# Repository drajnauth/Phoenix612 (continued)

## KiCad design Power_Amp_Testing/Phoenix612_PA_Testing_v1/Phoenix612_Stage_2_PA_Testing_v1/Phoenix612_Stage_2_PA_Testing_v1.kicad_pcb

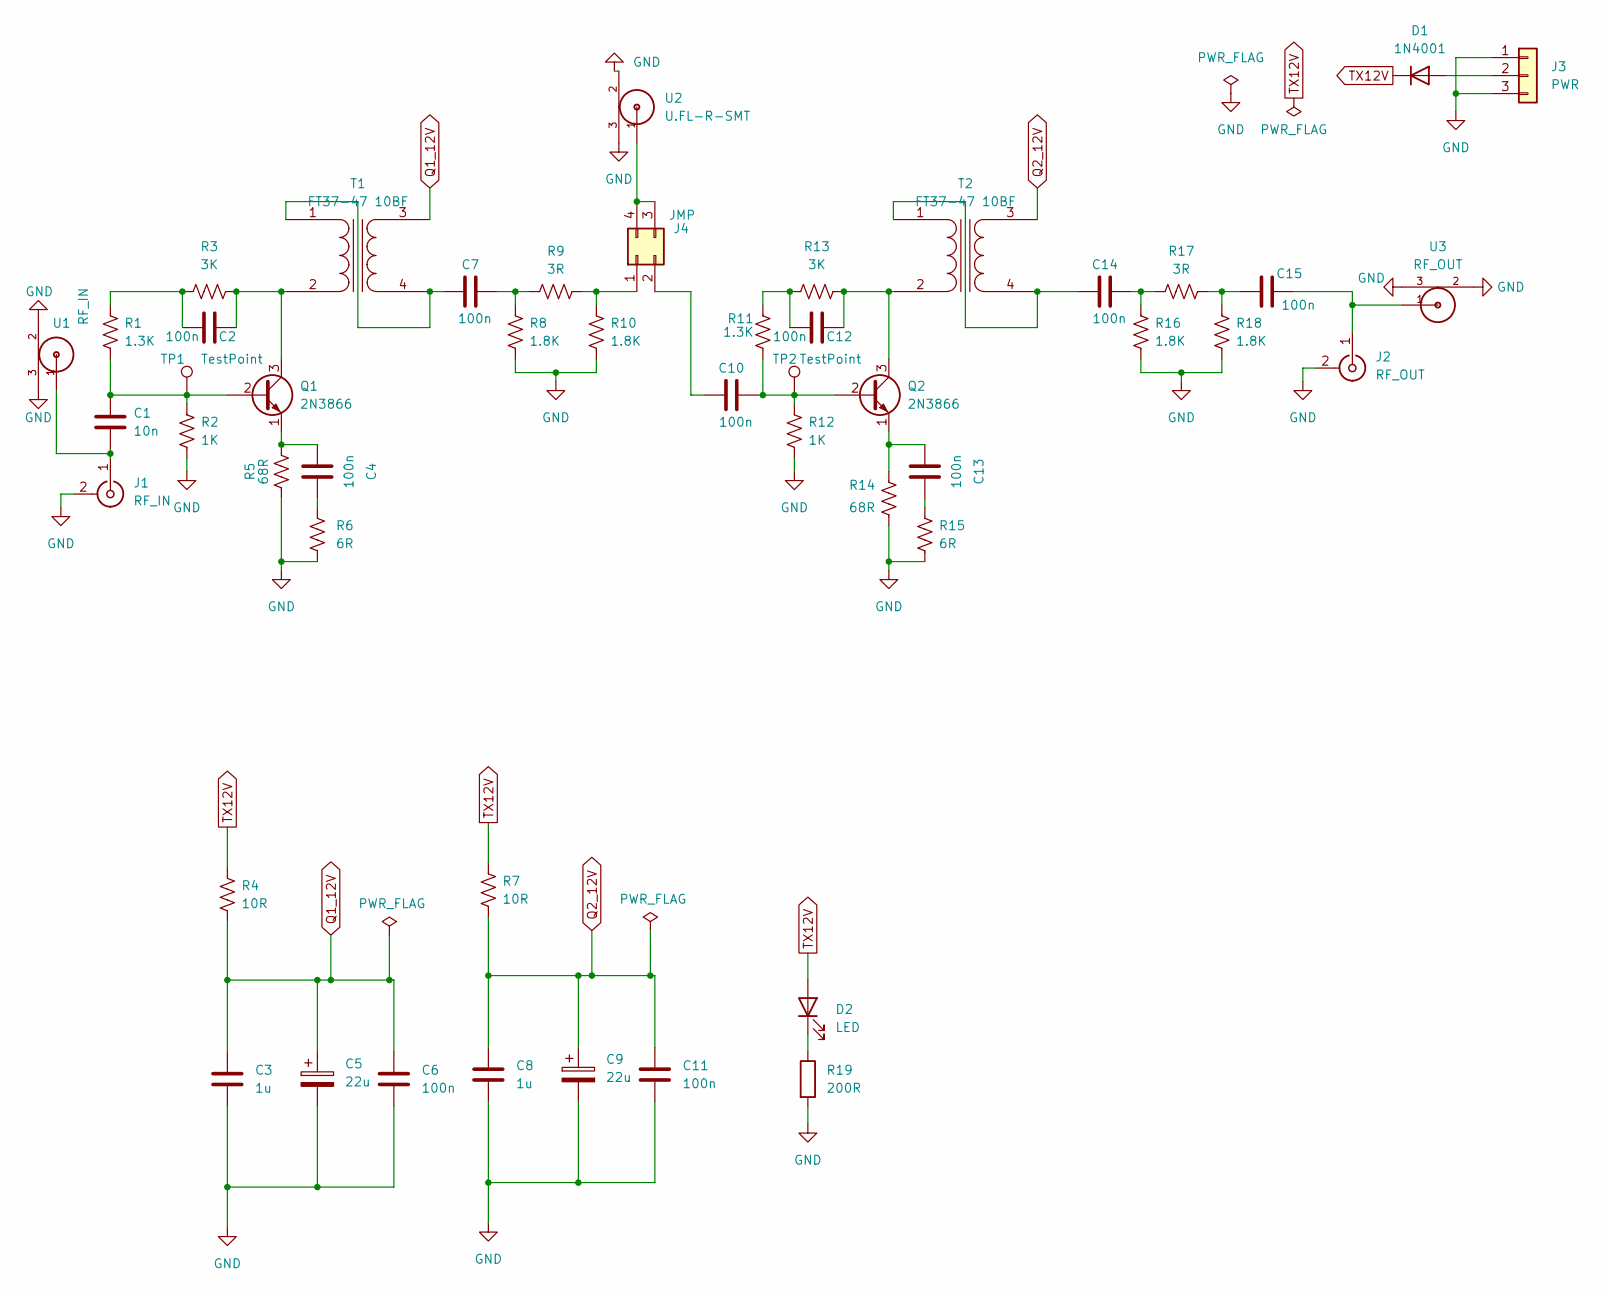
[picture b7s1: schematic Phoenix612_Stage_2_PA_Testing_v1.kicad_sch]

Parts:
C1: 10n; C_1206_3216Metric
C2, C4, C6, C7, C10, C11, C12, C13, C14, C15: 100n; C_1206_3216Metric
C3, C8: 1u; C_1206_3216Metric
C5, C9: 22u; CP_Radial_D8.0mm_P2.50mm
D1: 1N4001; D_DO-41_SOD81_P10.16mm_Horizontal
D2: LED; LED_D3.0mm
J1: RF_IN; SMA_Amphenol_901-144_Vertical
J2: RF_OUT; SMA_Amphenol_901-144_Vertical
J3: PWR; PinHeader_1x03_P2.54mm_Vertical
J4: JMP; PinHeader_2x02_P2.54mm_Vertical
Q1, Q2: 2N3866; TO-39-3
R1, R11: 1.3K; R_1206_3216Metric
R2, R12: 1K; R_1206_3216Metric
R3, R13: 3K; R_1206_3216Metric
R4, R7: 10R; R_1206_3216Metric
R5, R14: 68R; R_1206_3216Metric
R6, R15: 6R; R_1206_3216Metric
R8, R10, R16, R18: 1.8K; R_1206_3216Metric
R9, R17: 3R; R_1206_3216Metric
R19: 200R; R_1206_3216Metric
T1, T2: FT37-47 10BF; Transformer_Toroid_Horizontal_D10.5mm_Amidon-T37
TP1, TP2: TestPoint; Pin_D0.7mm_L6.5mm_W1.8mm_FlatFork
U1: RF_IN; U.FL-R-SMT
U2: U.FL-R-SMT
U3: RF_OUT; U.FL-R-SMT

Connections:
GND: C3.2, C5.2, C6.2, C8.2, C9.2, C11.2, J1.2 (Ext), J2.2 (Ext), J3.1, J3.3, R2.1, R5.1, R6.1, R8.1, R10.1, R12.1, R14.1, R15.1, R16.1, R18.1, R19.2, U1.2, U1.3, U2.2, U2.3, U3.2, U3.3
unnamed: C1.1, J1.1 (In), U1.1
unnamed: C1.2, Q1.2 (B), R1.1, R2.2, TP1.1
unnamed: C2.1, Q1.3 (C), R3.2, T1.2 (AB)
unnamed: C2.2, R1.2, R3.1
unnamed: C4.1, Q1.1 (E), R5.2
unnamed: C4.2, R6.2
unnamed: C7.1, R8.2, R9.1
unnamed: C7.2, T1.1 (AA), T1.4 (SA)
unnamed: C10.2, J4.2
unnamed: C12.1, Q2.3 (C), R13.2, T2.2 (AB)
unnamed: C12.2, R11.2, R13.1
unnamed: C13.1, Q2.1 (E), R14.2
unnamed: C13.2, R15.2
unnamed: C14.1, R16.2, R17.1
unnamed: C14.2, T2.1 (AA), T2.4 (SA)
unnamed: C15.1, J2.1 (In), U3.1
unnamed: C15.2, R17.2, R18.2
unnamed: D1.2 (A), J3.2
unnamed: D2.1 (K), R19.1
unnamed: J4.3, J4.4, U2.1
unnamed: C10.1, Q2.2 (B), R11.1, R12.2, TP2.1
unnamed: J4.1, R9.2, R10.2
Q1_12V: C3.1, C5.1, C6.1, R4.2, T1.3 (SB)
Q2_12V: C8.1, C9.1, C11.1, R7.2, T2.3 (SB)
TX12V: D1.1 (K), D2.2 (A), R4.1, R7.1

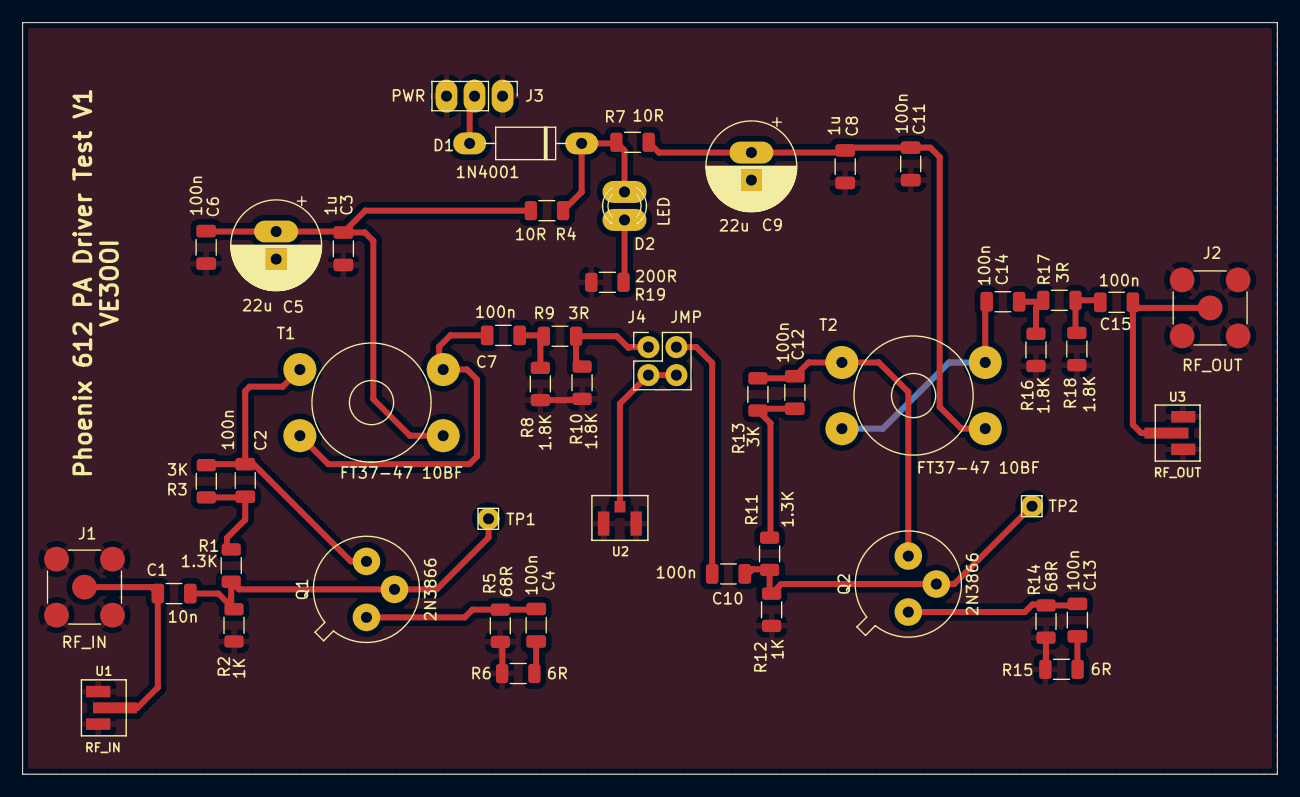
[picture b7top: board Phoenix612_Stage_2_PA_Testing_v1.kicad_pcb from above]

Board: 2 copper layers, 113.8 x 68.2 mm, 49 parts (0 on the bottom side), 26 nets.

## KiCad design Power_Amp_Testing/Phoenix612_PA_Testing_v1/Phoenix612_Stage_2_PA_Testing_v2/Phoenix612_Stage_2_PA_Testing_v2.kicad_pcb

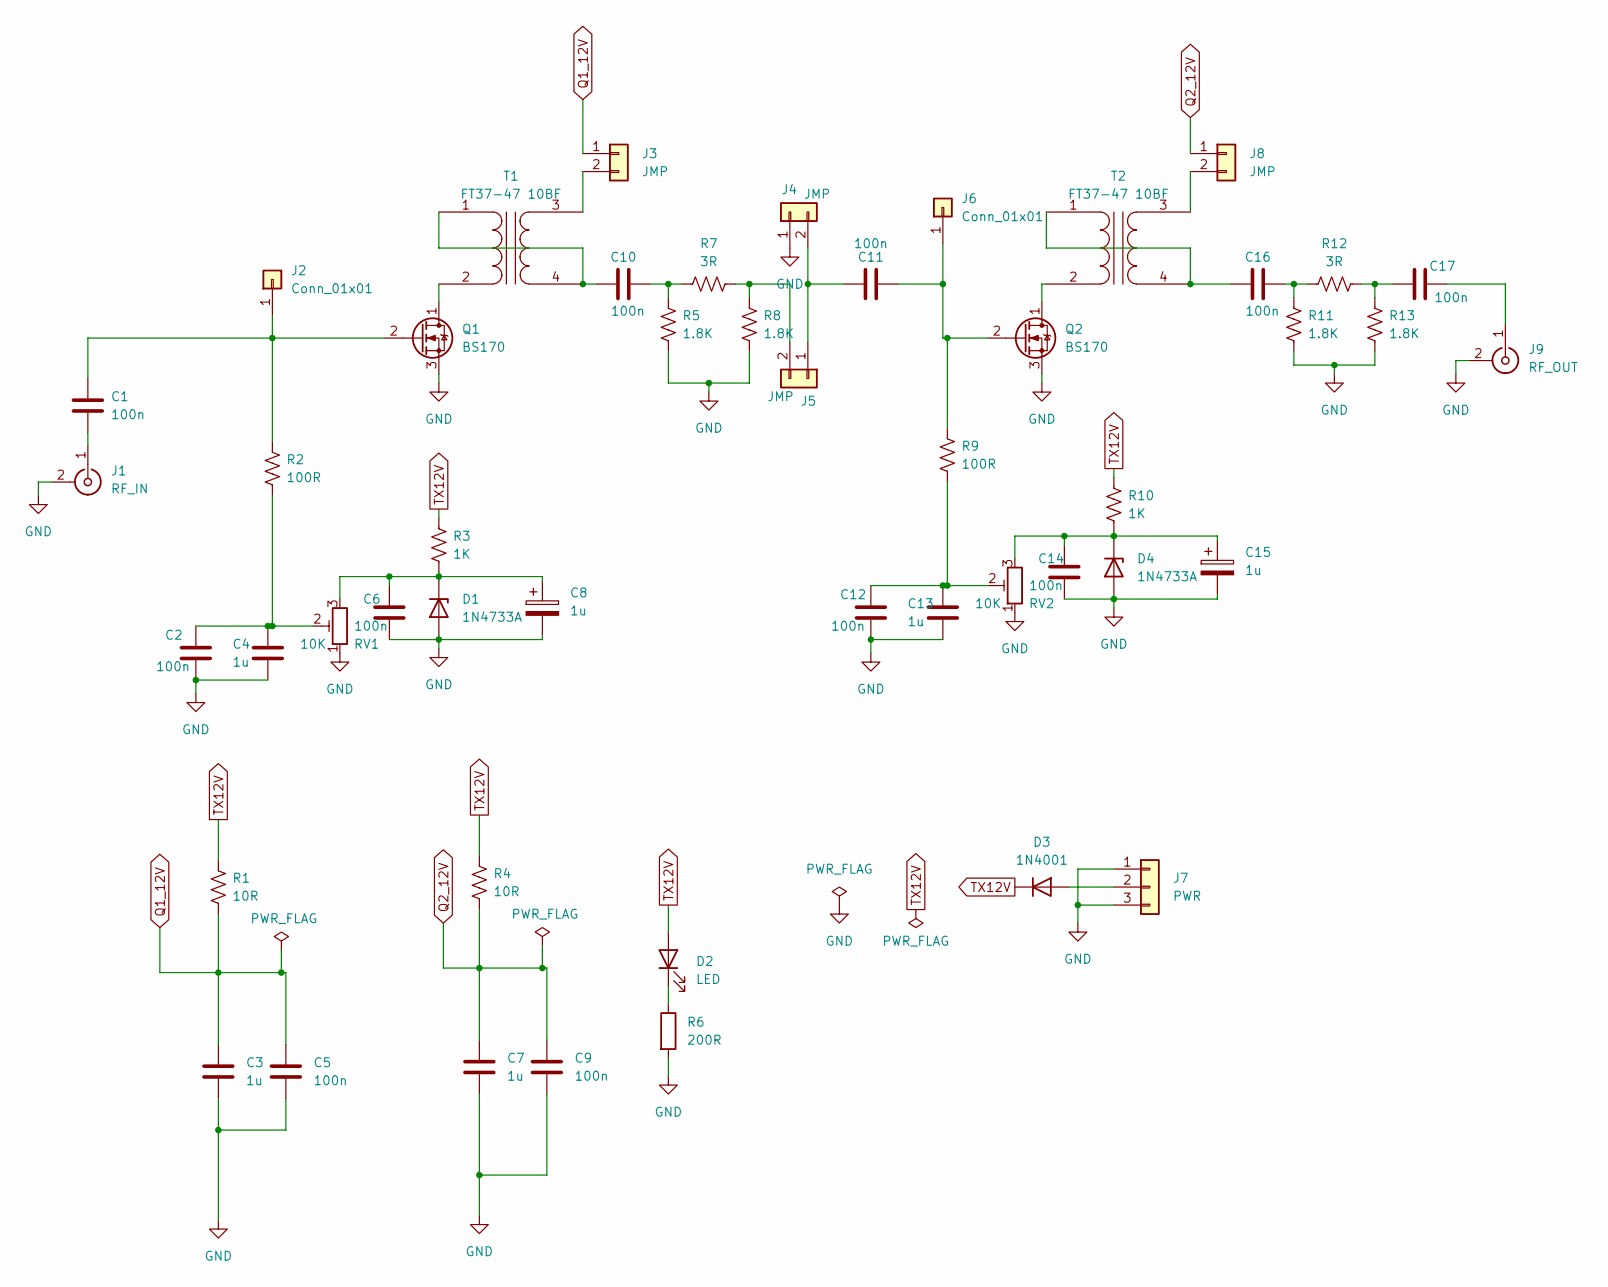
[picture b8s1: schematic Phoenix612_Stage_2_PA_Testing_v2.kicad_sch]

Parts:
C1, C2, C5, C6, C9, C10, C11, C12, C14, C16, C17: 100n; C_1206_3216Metric
C3, C4, C7, C13: 1u; C_1206_3216Metric
C8, C15: 1u; CP_Radial_D8.0mm_P2.50mm
D1, D4: 1N4733A; D_DO-41_SOD81_P10.16mm_Horizontal
D2: LED; LED_D3.0mm
D3: 1N4001; D_DO-41_SOD81_P10.16mm_Horizontal
J1: RF_IN; SMA_Amphenol_901-144_Vertical
J2, J6: Conn_01x01; PinHeader_1x01_P1.00mm_Vertical
J3, J4, J5, J8: JMP; PinHeader_1x02_P2.54mm_Vertical
J7: PWR; PinHeader_1x03_P2.54mm_Vertical
J9: RF_OUT; SMA_Amphenol_901-144_Vertical
Q1, Q2: BS170; TO-92_Inline_Wide
R1, R4: 10R; R_1206_3216Metric
R2, R9: 100R; R_1206_3216Metric
R3, R10: 1K; R_1206_3216Metric
R5, R8, R11, R13: 1.8K; R_1206_3216Metric
R6: 200R; R_1206_3216Metric
R7, R12: 3R; R_1206_3216Metric
RV1, RV2: 10K; Potentiometer_Bourns_3296W_Vertical
T1, T2: FT37-47 10BF; Transformer_Toroid_Horizontal_D10.5mm_Amidon-T37

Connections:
GND: C2.2, C3.2, C4.2, C5.2, C6.2, C7.2, C8.2, C9.2, C12.2, C13.2, C14.2, C15.2, D1.2 (A), D4.2 (A), J1.2 (Ext), J4.1, J7.1, J7.3, J9.2 (Ext), Q1.3 (S), Q2.3 (S), R5.1, R6.2, R8.1, R11.1, R13.1, RV1.1, RV2.1
unnamed: C1.1, J1.1 (In)
unnamed: C1.2, J2.1, Q1.2 (G), R2.2
unnamed: C2.1, C4.1, R2.1, RV1.2
unnamed: C6.1, C8.1, D1.1 (K), R3.2, RV1.3
unnamed: C10.1, R5.2, R7.1
unnamed: C10.2, T1.1 (AA), T1.4 (SA)
unnamed: C11.1, J6.1, Q2.2 (G), R9.2
unnamed: C11.2, J4.2, J5.1
unnamed: C12.1, C13.1, R9.1, RV2.2
unnamed: C14.1, C15.1, D4.1 (K), R10.2, RV2.3
unnamed: C16.1, R11.2, R12.1
unnamed: C16.2, T2.1 (AA), T2.4 (SA)
unnamed: C17.1, J9.1 (In)
unnamed: C17.2, R12.2, R13.2
unnamed: D2.1 (K), R6.1
unnamed: D3.2 (A), J7.2
unnamed: J3.2, T1.3 (SB)
unnamed: J5.2, R7.2, R8.2
unnamed: J8.2, T2.3 (SB)
unnamed: Q1.1 (D), T1.2 (AB)
unnamed: Q2.1 (D), T2.2 (AB)
Q1_12V: C3.1, C5.1, J3.1, R1.2
Q2_12V: C7.1, C9.1, J8.1, R4.2
TX12V: D2.2 (A), D3.1 (K), R1.1, R3.1, R4.1, R10.1

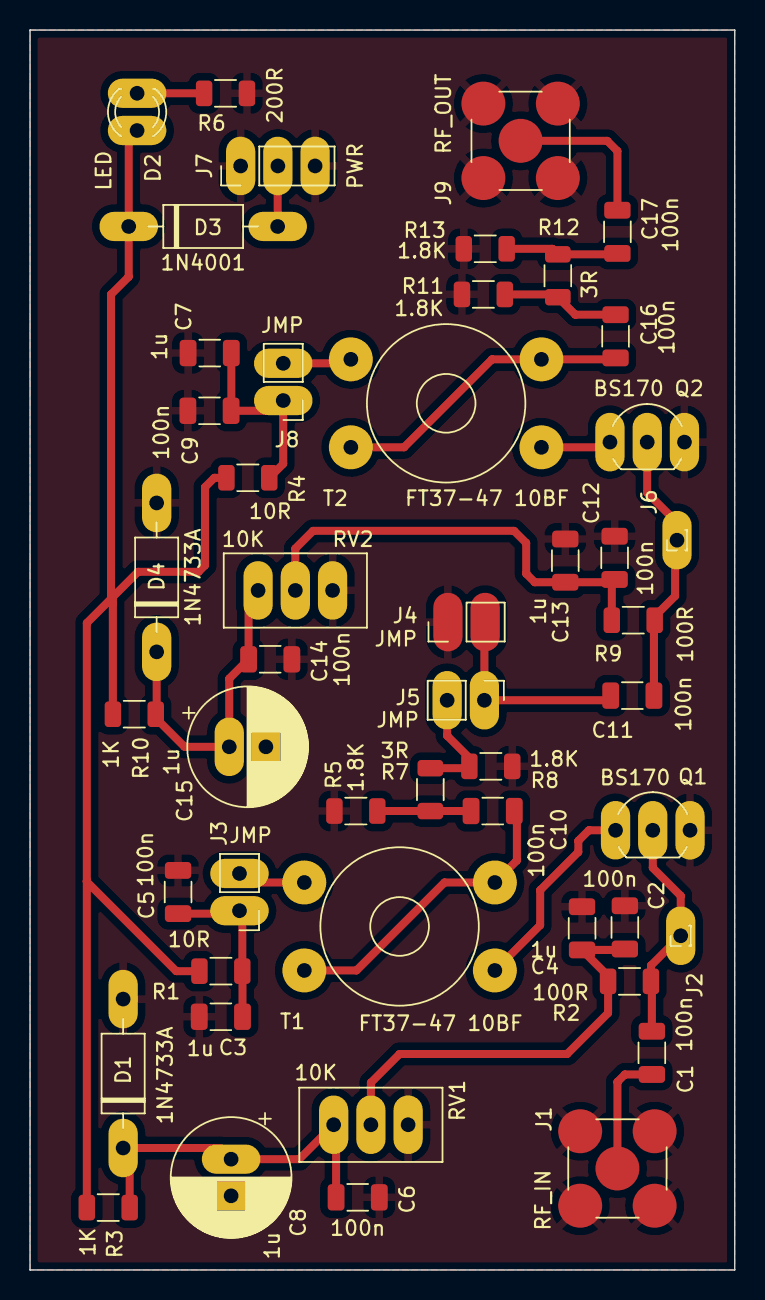
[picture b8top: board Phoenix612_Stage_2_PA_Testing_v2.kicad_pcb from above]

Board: 2 copper layers, 48.1 x 84.6 mm, 49 parts (0 on the bottom side), 25 nets.

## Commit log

2022-09-01 Add Legacy Diptrace
2022-09-01 Add legacy design docs
2022-09-01 Update License
2022-09-01 Add custom KiCad Lib
2022-09-02 Add AF Stage
2022-09-03 Continue Migration from D612
2022-09-12 Draft complete
2022-10-07 Proto Boards Complete
2023-02-21 Upload 21Mar23
2023-02-22 Update 22Feb23
2023-02-24 Update_24Feb23
2023-03-09 Update 9Mar23
2023-03-17 Update_17Mar23
2023-03-18 Update 17Mar23
2023-03-19 Update LT1253 Tx
2023-03-24 Update 24Mar23
2023-05-08 Cleanup 8May23
2023-05-08 Add Software 8May23
2023-05-08 Add Analysis 8May23
2023-05-17 Add PDF
